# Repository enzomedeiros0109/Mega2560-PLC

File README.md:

# Placa de Circuito Impresso

| Esquemático | Visão Superior (Top) | Visão Inferior (Bottom) |
| :---: | :---: | :---: |
|  |  |  |

## Descrição

Este projeto consiste no design de uma Placa de Circuito Impresso (PCB) voltada para aplicações de controle, automação e desenvolvimento. A placa integra diversas interfaces de entrada, saída e comunicação em um único hardware, tornando-a ideal para controle de processos industriais, automação residencial ou projetos acadêmicos avançados.

## Principais Recursos

Essa placa foi o projeto final da cadeira de Construção de Dispositivos Digitais do curso de Engenharia da Computação. Ela contém:

* **Processamento Central:** Espaço dedicado para o microcontrolador principal (U1) com pinos de programação/debug e cristal oscilador (Y1).
* **Interface de Usuário (IHM):**
    * **Teclado Matricial 4x4:** Matriz de 16 botões (SW2 a SW17) para entrada de dados e navegação.
    * **Display LCD:** Interface no topo da placa (U10) para conexão de displays LCD (ex: 16x2 ou 20x4).
* **Acionamento de Potência:**
    * **4x Relés Independentes:** (K1 a K4) com conectores tipo borne para acionamento seguro de cargas AC/DC externas.
* **Isolamento e Segurança:**
    * **Entradas/Saídas Optoisoladas:** CI's dedicados (U2 a U5) para proteção do circuito lógico contra ruídos e picos de tensão das interfaces externas.
* **Comunicação:**
    * **Porta Serial RS-232:** Conector DB9 (J11) em conjunto com o driver MAX232 (U9) para comunicação com CLP's, computadores e equipamentos legados.
* **Tratamento de Sinais Analógicos:**
    * Circuito com Amplificador Operacional (TL084 - U6) e múltiplos trimpots (RV1 a RV4) para calibração, condicionamento e ajuste de ganhos de sensores analógicos.
* **Conectividade:**
    * Múltiplos terminais de parafuso (screw terminals) nas bordas da placa para facilitar a ligação de sensores, fontes de alimentação e atuadores.

## Características do projeto

* **Software:** KiCAD
* **Camadas:** Placa de dupla face (Top e Bottom layers visíveis pelas trilhas vermelhas e azuis).

## Estrutura do Projeto

```text
├── assets/
│   └── schematic_view.jpeg   # Imagens e renderizações da placa
│   └── top_view.jpeg         # Parte superior da placa
│   └── bottom_view.jpeg      # Parte inferior da placa
├── gerbers                   # Arquivos para fabricação da PCB
├── pasta do projeto          # Pasta com projeto KiCAD
└── Planilha de preços.ods    # Planilha com preço e link dos componentes
```

## Como abrir o arquivo

1. Faça o clone do repositório.
2. Acesse a pasta `pasta do projeto` abra `av3.kicad_pro`.

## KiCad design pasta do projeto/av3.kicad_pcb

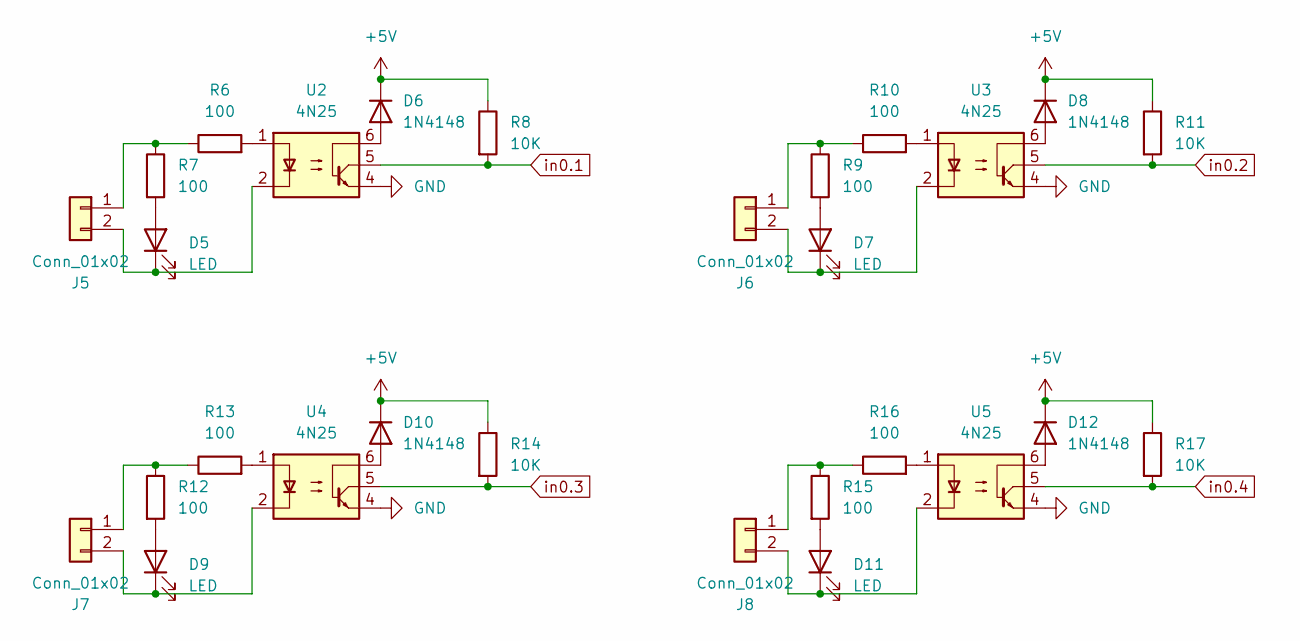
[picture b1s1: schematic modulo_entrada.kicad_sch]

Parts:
D5, D7, D9, D11: LED; LED_D3.0mm
D6, D8, D10, D12: 1N4148; D_DO-35_SOD27_P7.62mm_Horizontal
J5, J6, J7, J8: Conn_01x02; TerminalBlock_Phoenix_MKDS-1,5-2_1x02_P5.00mm_Horizontal
R6, R7, R9, R10, R12, R13, R15, R16: 100; R_1206_3216Metric_Pad1.30x1.75mm_HandSolder
R8, R11, R14, R17: 10K; R_1206_3216Metric_Pad1.30x1.75mm_HandSolder
U2, U3, U4, U5: 4N25; DIP-6_W7.62mm

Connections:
+5V: D6.1 (K), D8.1 (K), D10.1 (K), D12.1 (K), R8.1, R11.1, R14.1, R17.1; also elsewhere on the board
unnamed: D5.2 (A), R7.2
unnamed: D5.1 (K), J5.2, U2.2
unnamed: D6.2 (A), U2.6
unnamed: D7.2 (A), R9.2
unnamed: D7.1 (K), J6.2, U3.2
unnamed: D8.2 (A), U3.6
unnamed: D9.2 (A), R12.2
unnamed: D9.1 (K), J7.2, U4.2
unnamed: D10.2 (A), U4.6
unnamed: D11.2 (A), R15.2
unnamed: D11.1 (K), J8.2, U5.2
unnamed: D12.2 (A), U5.6
unnamed: J5.1, R6.1, R7.1
unnamed: J6.1, R9.1, R10.1
unnamed: J7.1, R12.1, R13.1
unnamed: J8.1, R15.1, R16.1
unnamed: R6.2, U2.1
unnamed: R10.2, U3.1
unnamed: R13.2, U4.1
unnamed: R16.2, U5.1
in0.1: R8.2, U2.5; also elsewhere on the board
in0.2: R11.2, U3.5; also elsewhere on the board
in0.3: R14.2, U4.5; also elsewhere on the board
in0.4: R17.2, U5.5; also elsewhere on the board

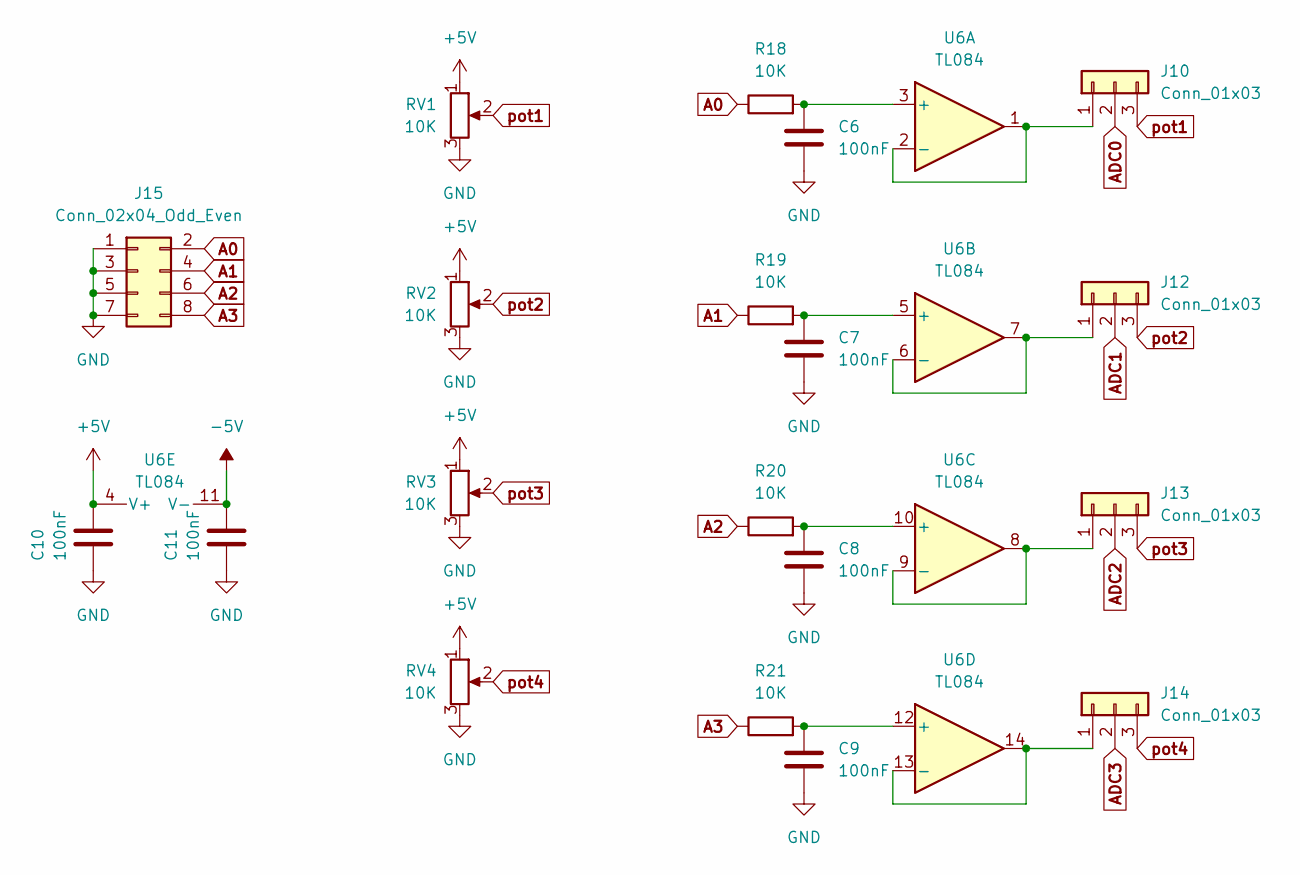
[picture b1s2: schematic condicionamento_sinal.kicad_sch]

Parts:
C6, C7, C8, C9, C10, C11: 100nF; C_0805_2012Metric
J10, J12, J13, J14: Conn_01x03; PinHeader_1x03_P2.54mm_Vertical
J15: Conn_02x04_Odd_Even; IDC-Header_2x04_P2.54mm_Vertical
R18, R19, R20, R21: 10K; R_Axial_DIN0207_L6.3mm_D2.5mm_P7.62mm_Horizontal
RV1, RV2, RV3, RV4: 10K; Potentiometer_Bourns_3296W_Vertical
U6: TL084; DIP-14_W7.62mm

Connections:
+5V: C10.1, RV1.1, RV2.1, RV3.1, RV4.1, U6.4 (V+); also elsewhere on the board
-5V: C11.1, U6.11 (V-)
A0: J15.2, R18.1
A1: J15.4, R19.1
A2: J15.6, R20.1
A3: J15.8, R21.1
ADC0: J10.2; also elsewhere on the board
ADC1: J12.2; also elsewhere on the board
ADC2: J13.2; also elsewhere on the board
ADC3: J14.2; also elsewhere on the board
unnamed: J10.1, U6.1, U6.2 (-)
unnamed: J12.1, U6.6 (-), U6.7
unnamed: J13.1, U6.8, U6.9 (-)
unnamed: J14.1, U6.13 (-), U6.14
unnamed: C6.1, R18.2, U6.3 (+)
unnamed: C7.1, R19.2, U6.5 (+)
unnamed: C8.1, R20.2, U6.10 (+)
unnamed: C9.1, R21.2, U6.12 (+)
pot1: J10.3, RV1.2
pot2: J12.3, RV2.2
pot3: J13.3, RV3.2
pot4: J14.3, RV4.2

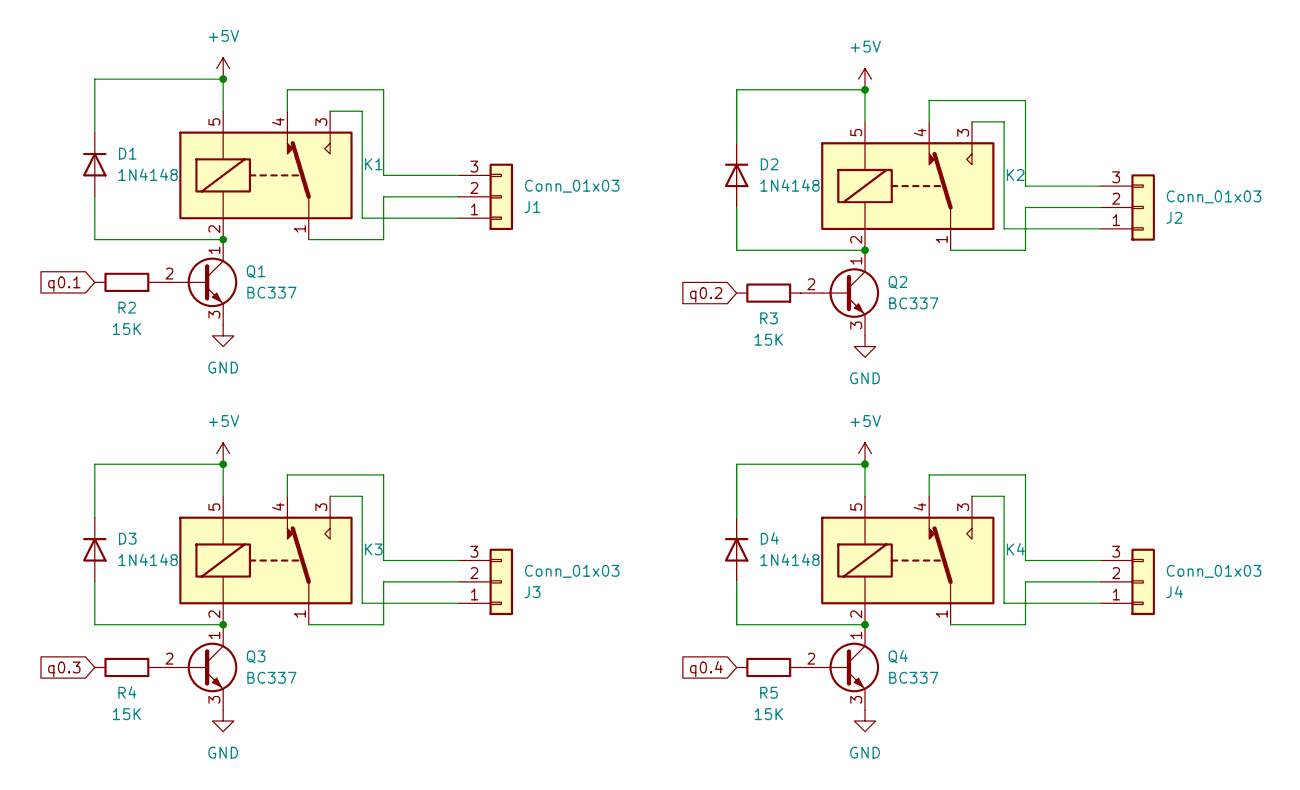
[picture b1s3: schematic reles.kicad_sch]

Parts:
D1, D2, D3, D4: 1N4148; D_DO-35_SOD27_P7.62mm_Horizontal
J1, J2, J3, J4: Conn_01x03; TerminalBlock_Phoenix_MKDS-1,5-3_1x03_P5.00mm_Horizontal
K1, K2, K3, K4: SANYOU_SRD_Form_C; Relay_SPDT_SANYOU_SRD_Series_Form_C
Q1, Q2, Q3, Q4: BC337; TO-92_Inline
R2, R3, R4, R5: 15K; R_Axial_DIN0207_L6.3mm_D2.5mm_P7.62mm_Horizontal

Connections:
+5V: D1.1 (K), D2.1 (K), D3.1 (K), D4.1 (K), K1.5, K2.5, K3.5, K4.5; also elsewhere on the board
unnamed: D1.2 (A), K1.2, Q1.1 (C)
unnamed: D2.2 (A), K2.2, Q2.1 (C)
unnamed: D3.2 (A), K3.2, Q3.1 (C)
unnamed: D4.2 (A), K4.2, Q4.1 (C)
unnamed: J1.1, K1.3
unnamed: J1.2, K1.1
unnamed: J1.3, K1.4
unnamed: J2.1, K2.3
unnamed: J2.2, K2.1
unnamed: J2.3, K2.4
unnamed: J3.1, K3.3
unnamed: J3.2, K3.1
unnamed: J3.3, K3.4
unnamed: J4.1, K4.3
unnamed: J4.2, K4.1
unnamed: J4.3, K4.4
unnamed: Q1.2 (B), R2.2
unnamed: Q2.2 (B), R3.2
unnamed: Q3.2 (B), R4.2
unnamed: Q4.2 (B), R5.2
q0.1: R2.1; also elsewhere on the board
q0.2: R3.1; also elsewhere on the board
q0.3: R4.1; also elsewhere on the board
q0.4: R5.1; also elsewhere on the board

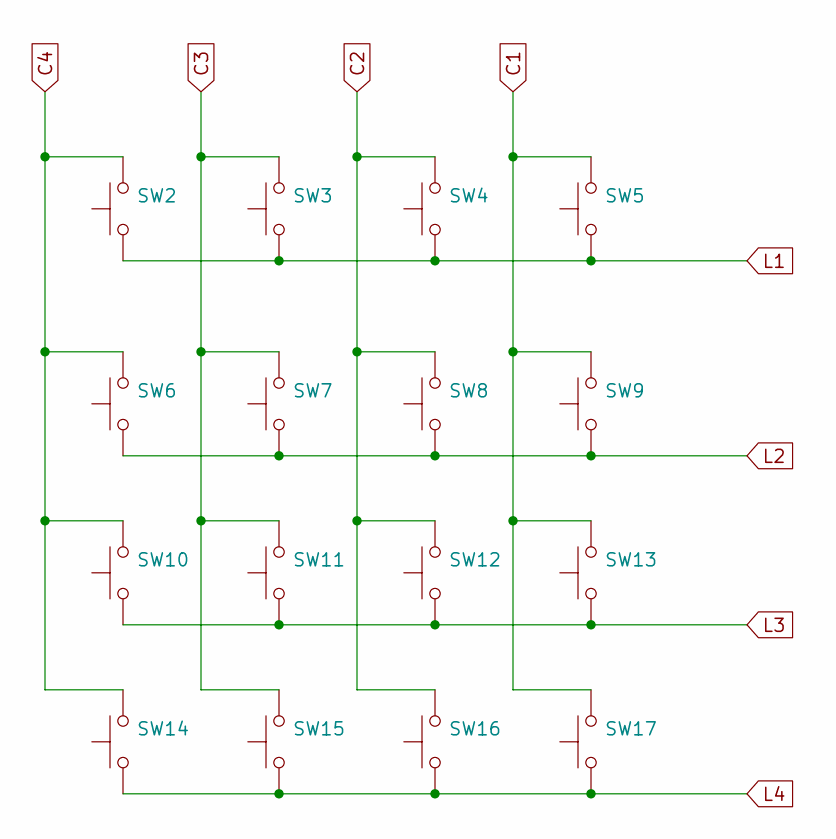
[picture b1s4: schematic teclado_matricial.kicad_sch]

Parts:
SW2, SW3, SW4, SW5, SW6, SW7, SW8, SW9, SW10, SW11, SW12, SW13, SW14, SW15, SW16, SW17: SW_Omron_B3FS; SW_Push_1P1T_NO_CK_KSC7xxJ

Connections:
C1: SW5.2, SW9.2, SW13.2, SW17.2; also elsewhere on the board
C2: SW4.2, SW8.2, SW12.2, SW16.2; also elsewhere on the board
C3: SW3.2, SW7.2, SW11.2, SW15.2; also elsewhere on the board
C4: SW2.2, SW6.2, SW10.2, SW14.2; also elsewhere on the board
L1: SW2.1, SW3.1, SW4.1, SW5.1; also elsewhere on the board
L2: SW6.1, SW7.1, SW8.1, SW9.1; also elsewhere on the board
L3: SW10.1, SW11.1, SW12.1, SW13.1; also elsewhere on the board
L4: SW14.1, SW15.1, SW16.1, SW17.1; also elsewhere on the board

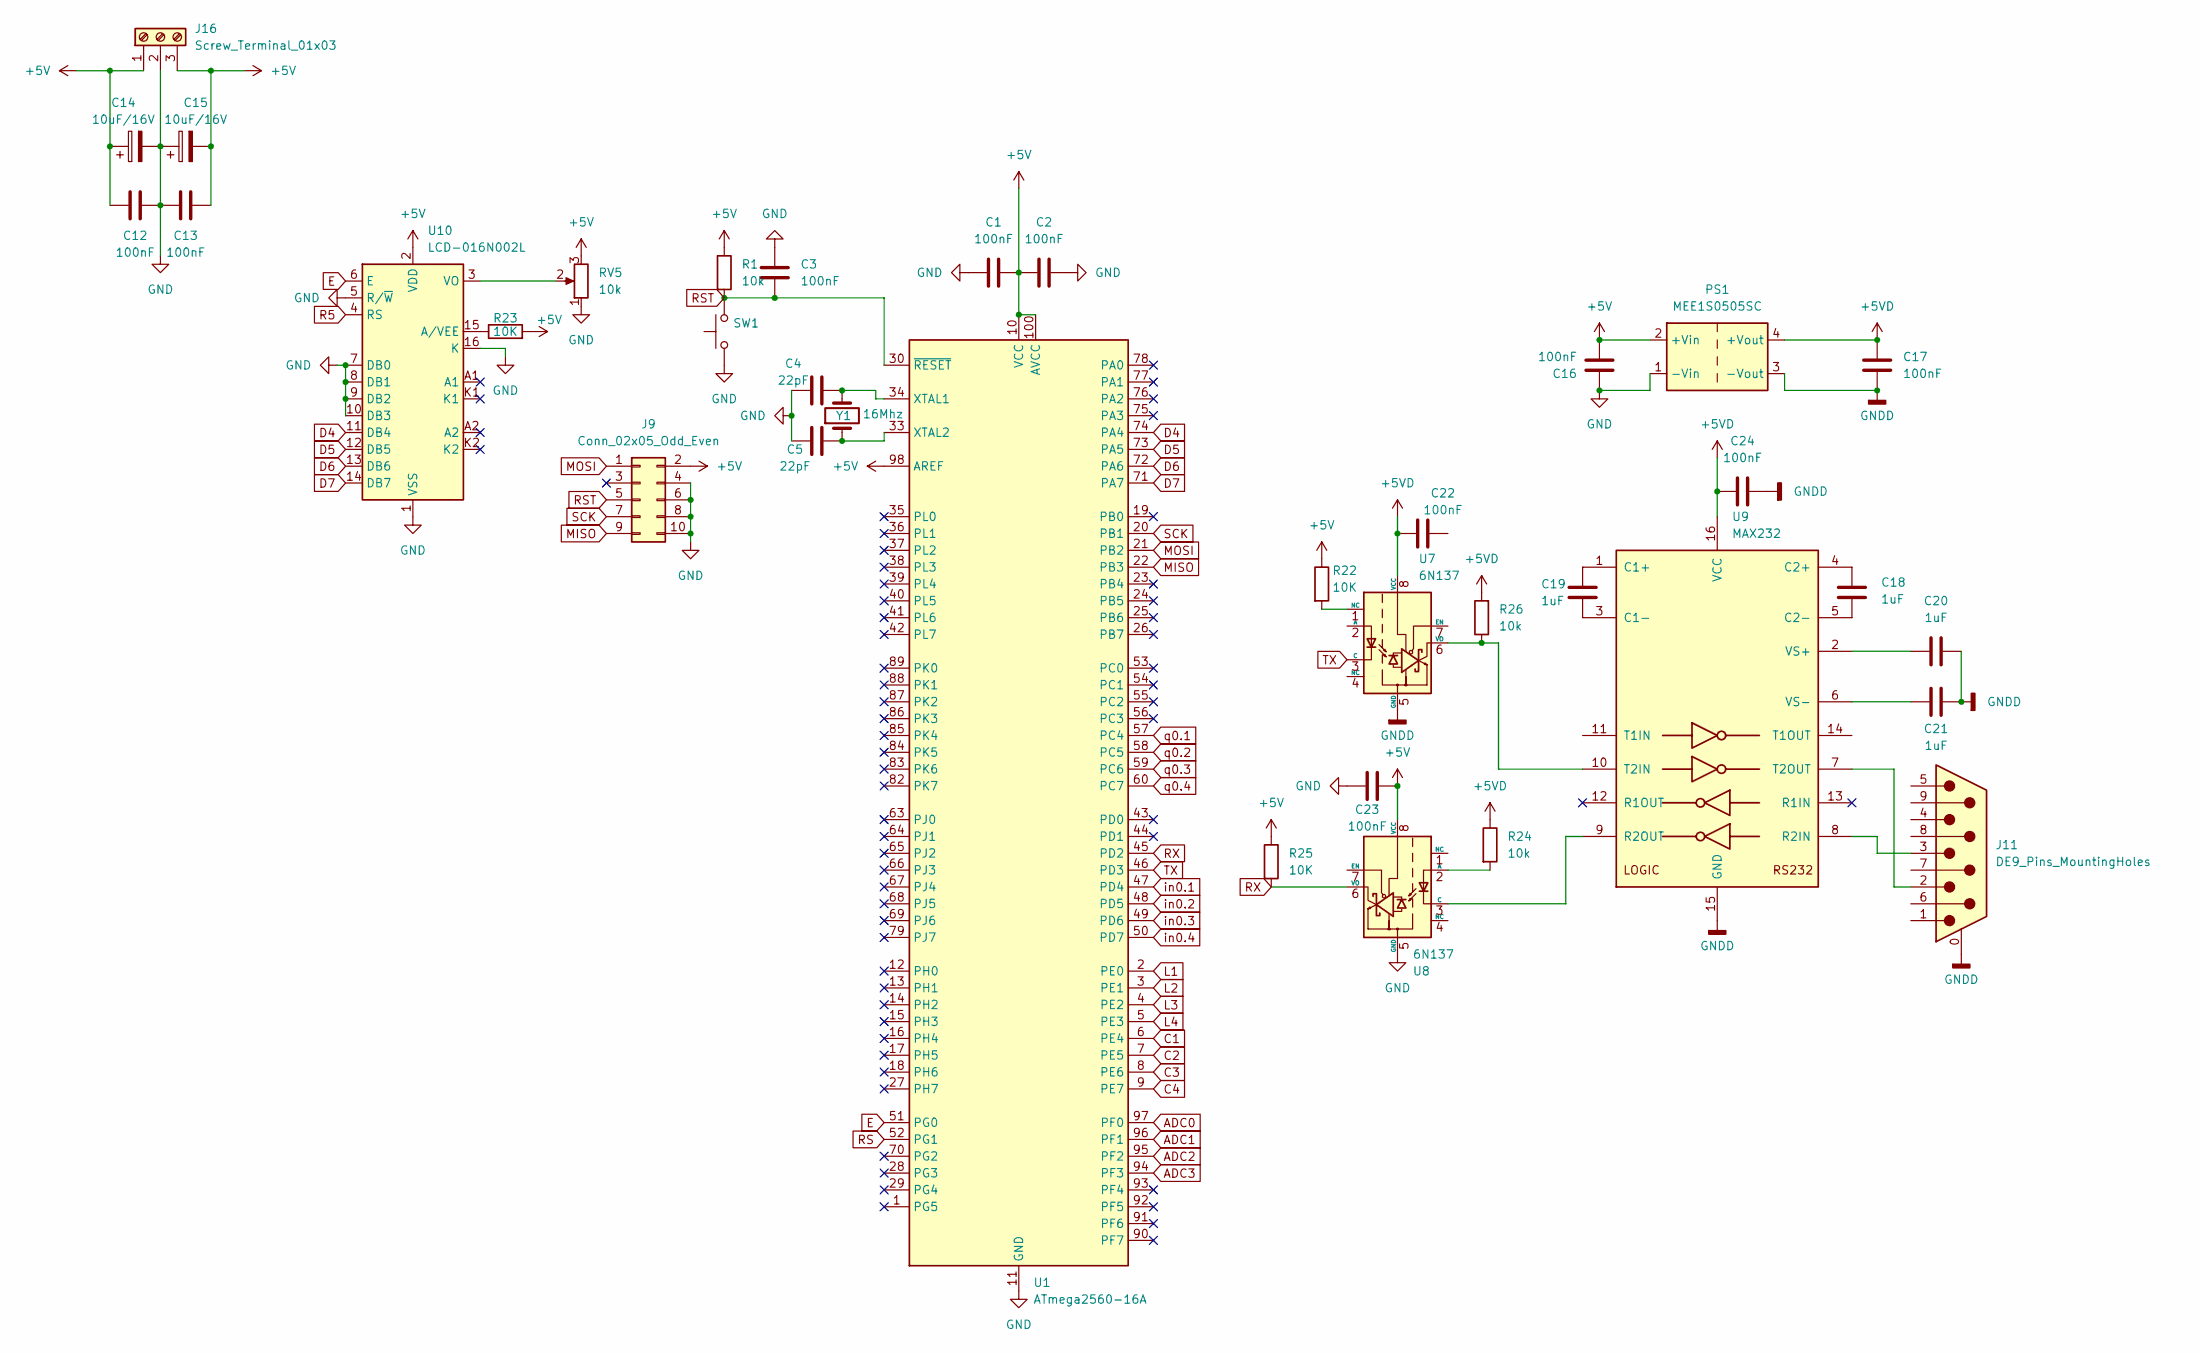
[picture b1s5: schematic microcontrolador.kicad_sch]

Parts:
C1, C2, C3, C12, C13, C16, C17, C22, C23, C24: 100nF; C_0805_2012Metric
C4, C5: 22pF; C_0805_2012Metric
C14, C15: 10uF/16V; CP_Radial_D5.0mm_P2.50mm
C18, C19, C20, C21: 1uF; CP_Radial_D4.0mm_P2.00mm
J9: Conn_02x05_Odd_Even; PinHeader_2x05_P2.54mm_Vertical
J11: DE9_Pins_MountingHoles; DSUB-9_Pins_Vertical_P2.77x2.84mm_MountingHoles
J16: Screw_Terminal_01x03; TerminalBlock_Phoenix_MKDS-1,5-3-5.08_1x03_P5.08mm_Horizont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
PS1: MEE1S0505SC; Converter_DCDC_Murata_CRE1xxxxxxSC_THT
R1, R24, R26: 10k; R_Axial_DIN0207_L6.3mm_D2.5mm_P7.62mm_Horizontal
R22, R23, R25: 10K; R_Axial_DIN0207_L6.3mm_D2.5mm_P7.62mm_Horizontal
RV5: 10k; Potentiometer_Bourns_3296W_Vertical
SW1: SW_MEC_5G; SW_Push_1P1T_NO_CK_KSC7xxJ
U1: ATmega2560-16A; TQFP-100_14x14mm_P0.5mm
U7, U8: 6N137; DIP-8_W7.62mm
U9: MAX232; DIP-16_W7.62mm
U10: LCD-016N002L
Y1: 16Mhz; Resonator-2Pin_W10.0mm_H5.0mm

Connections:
+5V: C1.2, C2.1, C12.1, C13.2, C14.1, C15.2, C16.1, C23.2, J9.2, J16.1, J16.3, PS1.2 (+Vin), R1.1, R22.1, R23.2, R25.1, RV5.3, U1.10 (VCC), U1.31 (VCC), U1.61 (VCC), U1.80 (VCC), U1.98 (AREF), U1.100 (AVCC), U8.8 (VCC), U10.2 (VDD); also elsewhere on the board
+5VD: C17.1, C22.1, C24.1, PS1.4 (+Vout), R24.1, R26.2, U7.8 (VCC), U9.16 (VCC)
ADC0: U1.97 (PF0); also elsewhere on the board
ADC1: U1.96 (PF1); also elsewhere on the board
ADC2: U1.95 (PF2); also elsewhere on the board
ADC3: U1.94 (PF3); also elsewhere on the board
C1: U1.6 (PE4); also elsewhere on the board
C2: U1.7 (PE5); also elsewhere on the board
C3: U1.8 (PE6); also elsewhere on the board
C4: U1.9 (PE7); also elsewhere on the board
D4: U1.74 (PA4), U10.11 (DB4)
D5: U1.73 (PA5), U10.12 (DB5)
D6: U1.72 (PA6), U10.13 (DB6)
D7: U1.71 (PA7), U10.14 (DB7)
E: U1.51 (PG0), U10.6 (E)
GNDD: C17.2, C20.2, C21.2, C24.2, J11.0 (PAD), PS1.3 (-Vout), U7.5 (GND), U9.15 (GND)
L1: U1.2 (PE0); also elsewhere on the board
L2: U1.3 (PE1); also elsewhere on the board
L3: U1.4 (PE2); also elsewhere on the board
L4: U1.5 (PE3); also elsewhere on the board
unnamed: C4.2, U1.34 (XTAL1), Y1.2
unnamed: C5.2, U1.33 (XTAL2), Y1.1
unnamed: R26.1, U7.6 (VO), U9.10 (T2IN)
unnamed: R24.2, U8.2 (A)
unnamed: U8.3 (C), U9.9 (R2OUT)
unnamed: C19.1, U9.1 (C1+)
unnamed: C19.2, U9.3 (C1-)
unnamed: C18.1, U9.4 (C2+)
unnamed: C18.2, U9.5 (C2-)
unnamed: J11.3, U9.8 (R2IN)
unnamed: J11.2, U9.7 (T2OUT)
unnamed: C20.1, U9.2 (VS+)
unnamed: C21.1, U9.6 (VS-)
unnamed: R23.1, U10.15 (A/VEE)
unnamed: RV5.2, U10.3 (VO)
R5: U10.4 (RS)
RS: U1.52 (PG1)
RX: R25.2, U1.45 (PD2), U8.6 (VO)
SCK: J9.7, U1.20 (PB1)
TX: U1.46 (PD3), U7.3 (C)
in0.1: U1.47 (PD4); also elsewhere on the board
in0.2: U1.48 (PD5); also elsewhere on the board
in0.3: U1.49 (PD6); also elsewhere on the board
in0.4: U1.50 (PD7); also elsewhere on the board
q0.1: U1.57 (PC4); also elsewhere on the board
q0.2: U1.58 (PC5); also elsewhere on the board
q0.3: U1.59 (PC6); also elsewhere on the board
q0.4: U1.60 (PC7); also elsewhere on the board

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
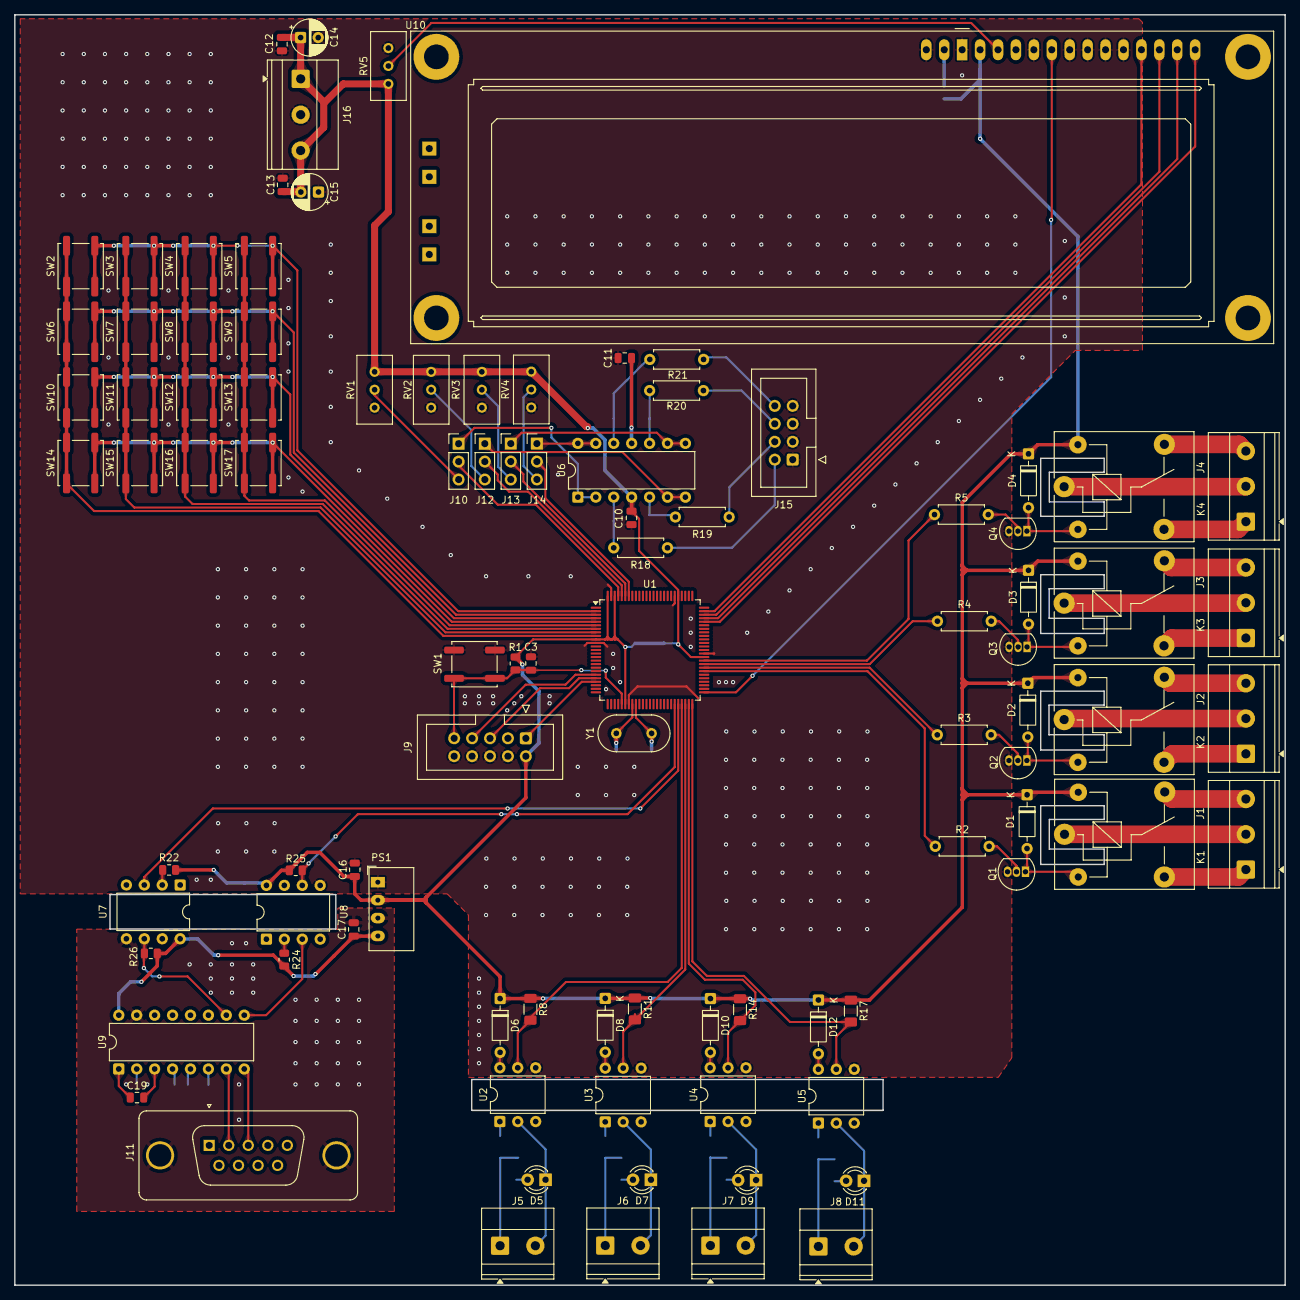
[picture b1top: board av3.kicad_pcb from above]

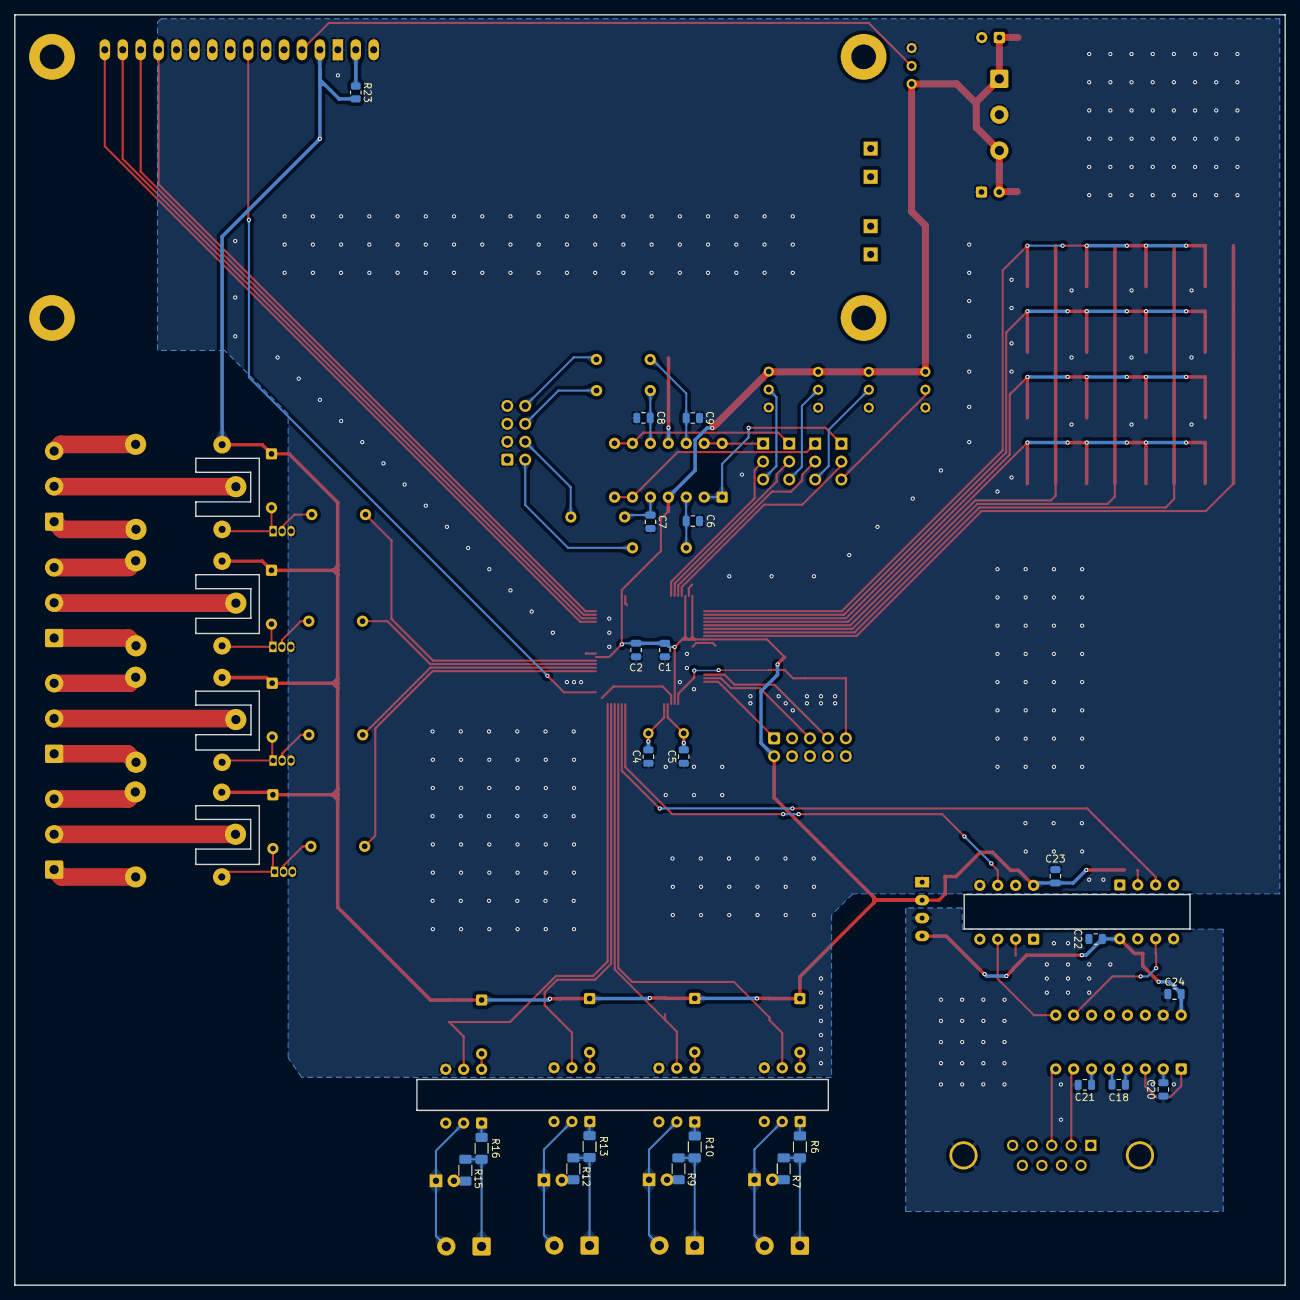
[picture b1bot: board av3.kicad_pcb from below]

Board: 2 copper layers, 180.0 x 180.0 mm, 120 parts (23 on the bottom side), 108 nets.

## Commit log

2026-05-08 Adds .zip
2026-05-10 FEAT: Adiciona as folhas de projeto restantes (reles, modulo_entrada e condicionamento_sinal)
2026-05-13 FEAT: Adição das footprints dos capacitores (C) e screw_terminals (J)
2026-05-27 Alteração do footprint do PS1 e inicio da PCB
2026-05-28 Mudança de footprints e mudança na PCB
2026-06-02 Algumas trilhas feitas
2026-06-03 Finaliza a organização dos componentes na PCB, ajusta footprints
2026-06-07 Orçamento de montagem e outros orçamentos
2026-06-11 Finalização do orçamento e das malhas
2026-06-11 final, final mesmo
2026-06-13 Corrige malha de ground, trilhas dos relés e tensão, adiciona furos na placa
2026-06-13 Atualiza o README
2026-06-13 Alterações nas malhas GND/GNDD, mudança de trilha nos relés, tensão e adição de furos na placa
2026-06-14 Corrige erro da PCI
2026-06-19 Remove vias dos pads de componentes SMD e corrige caminho de trilhas
